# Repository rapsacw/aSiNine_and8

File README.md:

# aSiNine_and8
Small (46.5x73.2mm) BM1397 based standalone bitcoin miner

Revision 04k, remarks:
- PWM fan: do not populate T2,JP1 & R10, unless you want to use that feature (no software support yet), replace T2 with a mosfet if you want to use it, a transistor will pull gpio9 low at startup locking the esp in programming mode.
- programming first time: some esp's will not enter programming mode automatically, in that case short gpio9 to ground at power-up (gpio9 is connected to the encircled via close to the esp32-c3). Updating the firmware is best done through OTA @ <your miner's ip address>/update). You can also flash the esp with the ElegantOTA demo and then flash it first time over the air.
- Powering the miner: use a 5V/3A usb charger for low power application (upto ~250GHs). If you want more powerrr use the screw terminal to connect a 9-12V power supply. I use a usb trigger (like https://www.aliexpress.com/item/1005004562492420.html) set to 9V connected to a usb charger with PD (use a high efficiency charger like https://www.aliexpress.com/item/1005004530223949.html). IMPORTANT: only connect the miner with ONE of the power inputs. Powering the miner with more than 5V and connecting it to a PC will damage the miner and the pc!!!!
- Cooling: I use a 7cm piece of https://www.aliexpress.com/item/1005001772072504.html with a 5cm 5V fan (runs on 3.3V when connected to X1) like https://www.aliexpress.com/item/1005003059434065.html strapped to the heatsink and board with tie wraps. Don't forget to use some (non-conductive!) thermal compound. This fan/heatsink combo will allow the miner to be run at upto 320GHs while staying (just) below my max asic temperature of 60C and is virtually silent.
- The firmware used is bm1397.ino.bin included in this repo, and can be used until I update & publish the source code of my firmware.

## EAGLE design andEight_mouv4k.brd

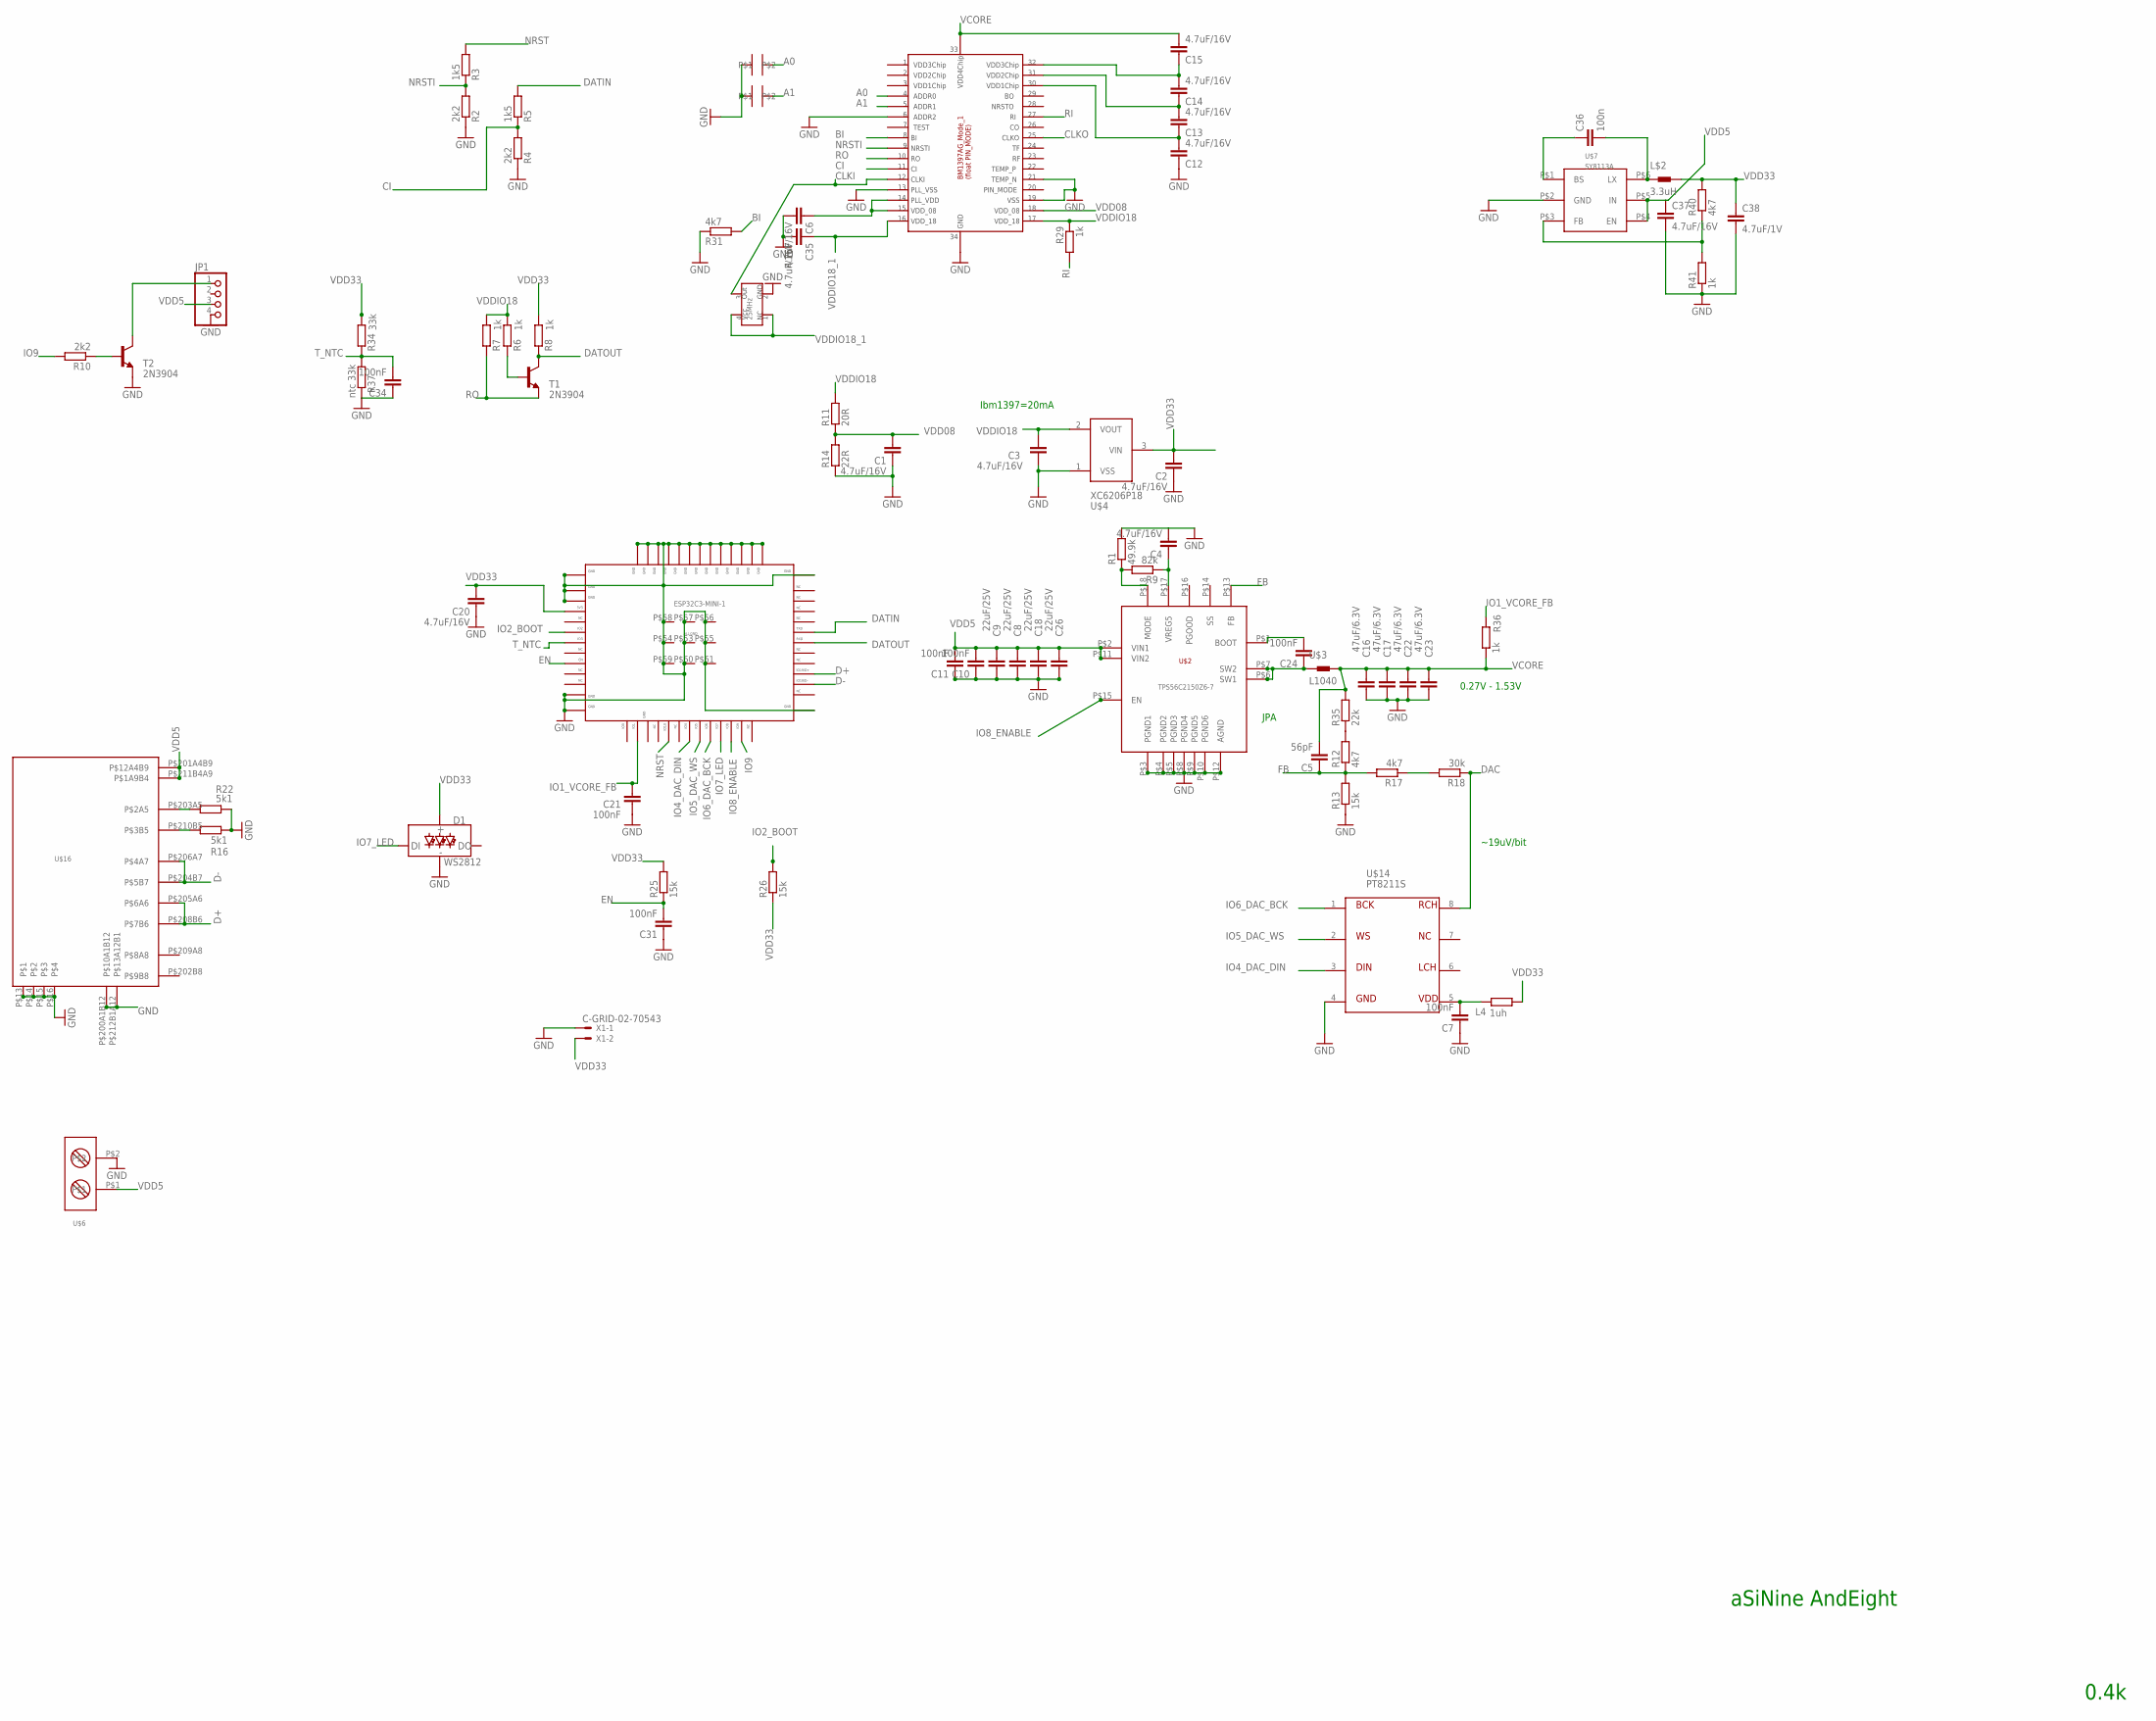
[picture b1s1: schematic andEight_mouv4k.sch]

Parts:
A0, A1: SOLDERJUMPER
C1, C2, C3, C4, C6, C12, C13, C14, C15, C35, C37: 4.7uF/16V; C0402
C5: 56pF; C0402
C7, C10, C11, C24, C31, C34: 100nF; C0402
C8, C9, C18, C26: 22uF/25V; C0805
C16, C17, C22, C23: 47uF/6.3V; C0805
C20: 4.7uF/16V; C0603
C21: 100nF; C0603
C36: 100n; C0402
C38: 4.7uF/1V; C0402
D1: WS2812; WS2812-5X5-4PIN
ESP32C3-MINI-1: ESP32-C3-MINI-1; ESP32C3MINI
JP1: PINHD-1X4/90; 1X04/90
L4: 1uh; R0402
L$2: 3.3uH; NR201610
R1: 49.9k; R0402
R2, R4, R10: 2k2; R0402
R3, R5: 1k5; R0402
R6, R7, R8, R29, R36, R41: 1k; R0402
R9: 82k; R0402
R11: 20R; R0402
R12, R17, R31, R40: 4k7; R0402
R13, R25, R26: 15k; R0402
R14: 22R; R0402
R16, R22: 5k1; R0402
R18: 30k; R0402
R34: 33k; R0603
R35: 22k; R0402
R37: ntc 33k; R0402
T1, T2: 2N3904; SOT23
U$1: BM1397-1; BM1391
U$2: TPS56C2150Z6-7; VQFN-HR
U$3: L1040
U$4: XC6206P18; SOT23
U$6: DG301-50
U$7: SY8113A; SOT23L-6
U$14: PT8211S; SO-8
U$16: USBCTHT; USBCSMTTHT
U$22: 25MHz; 3225
X1: C-GRID-02-70543; 70543-02

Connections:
A0: A0.P$1, U$1.P$4
A1: A1.P$1, U$1.P$5
BI: R31.2, U$1.P$8
CI: R4.2, R5.1, U$1.P$11
CLKI: U$1.P$12, U$22.P$3
CLKO: U$1.P$25
D+: ESP32C3-MINI-1.P$27, U$16.P$205A6 (P$6A6), U$16.P$208B6 (P$7B6)
D-: ESP32C3-MINI-1.P$26, U$16.P$204B7 (P$5B7), U$16.P$206A7 (P$4A7)
DAC: R18.1, U$14.8
DATIN: ESP32C3-MINI-1.P$31, R5.2
DATOUT: ESP32C3-MINI-1.P$30, R8.1, T1.3 (C)
EN: C31.2, ESP32C3-MINI-1.P$8, R25.1
FB: C5.1, R12.1, R13.2, R17.2, U$2.P$13 (FB)
GND: A0.P$2, A1.P$2, C1.1, C2.1, C3.1, C4.2, C6.2, C7.1, C8.2, C9.2, C10.1, C11.1, C12.1, C16.2, C17.2, C18.2, C20.1, C21.1, C22.2, C23.2, C26.2, C31.1, C34.1, C35.2, C37.2, C38.2, D1.GND, ESP32C3-MINI-1.P$1, ESP32C3-MINI-1.P$2, ESP32C3-MINI-1.P$11, ESP32C3-MINI-1.P$36, ESP32C3-MINI-1.P$37, ESP32C3-MINI-1.P$38, ESP32C3-MINI-1.P$39, ESP32C3-MINI-1.P$40, ESP32C3-MINI-1.P$41, ESP32C3-MINI-1.P$42, ESP32C3-MINI-1.P$43, ESP32C3-MINI-1.P$44, ESP32C3-MINI-1.P$45, ESP32C3-MINI-1.P$46, ESP32C3-MINI-1.P$47, ESP32C3-MINI-1.P$48, ESP32C3-MINI-1.P$49, ESP32C3-MINI-1.P$50, ESP32C3-MINI-1.P$51, ESP32C3-MINI-1.P$52, ESP32C3-MINI-1.P$53, ESP32C3-MINI-1.P$54, ESP32C3-MINI-1.P$55, ESP32C3-MINI-1.P$56, ESP32C3-MINI-1.P$57, ESP32C3-MINI-1.P$58, ESP32C3-MINI-1.P$59, ESP32C3-MINI-1.P$60, ESP32C3-MINI-1.P$61, JP1.4, R1.2, R2.1, R4.1, R13.1, R14.2, R16.2, R22.2, R31.1, R37.1, R41.1, T2.2 (E), U$1.P$6, U$1.P$13, U$1.P$19, U$1.P$21, U$1.P$34, U$2.P$3 (PGND1), U$2.P$4 (PGND2), U$2.P$5 (PGND3), U$2.P$8 (PGND4), U$2.P$9 (PGND5), U$2.P$10 (PGND6), U$2.P$12 (AGND), U$4.1 (VSS), U$6.P$2, U$7.P$2 (GND), U$14.4, U$16.P$13, U$16.P$14, U$16.P$15, U$16.P$16, U$16.P$200A1B12 (P$10A1B12), U$16.P$212B1A12 (P$13A12B1), U$22.P$2, X1.1
IO1_VCORE_FB: C21.2, ESP32C3-MINI-1.P$13, R36.2
IO2_BOOT: ESP32C3-MINI-1.P$5, R26.2
IO4_DAC_DIN: ESP32C3-MINI-1.P$18, U$14.3
IO5_DAC_WS: ESP32C3-MINI-1.P$19, U$14.2
IO6_DAC_BCK: ESP32C3-MINI-1.P$20, U$14.1
IO7_LED: D1.DI, ESP32C3-MINI-1.P$21
IO8_ENABLE: ESP32C3-MINI-1.P$22, U$2.P$15 (EN)
IO9: ESP32C3-MINI-1.P$23, R10.2
unnamed: R10.1, T2.1 (B)
unnamed: C24.2, U$2.P$1 (BOOT)
unnamed: C24.1, U$2.P$6 (SW1), U$2.P$7 (SW2), U$3.P$1 (1)
unnamed: C4.1, R9.1, U$2.P$17 (VREG5)
unnamed: R1.1, R9.2, U$2.P$18 (MODE)
unnamed: JP1.1, T2.3 (C)
unnamed: C36.1, U$7.P$1 (BS)
unnamed: C36.2, L$2.P$1 (1), U$7.P$6 (LX)
unnamed: R40.1, R41.2, U$7.P$3 (FB)
unnamed: R16.1, U$16.P$210B5 (P$3B5)
unnamed: R22.1, U$16.P$203A5 (P$2A5)
unnamed: R6.1, T1.1 (B)
unnamed: R12.2, R35.1
unnamed: R17.1, R18.2
NRST: ESP32C3-MINI-1.P$16, R3.2
NRSTI: R2.2, R3.1, U$1.P$9
P$5: C7.2, L4.2, U$14.5
RI: R29.2, U$1.P$27
RO: R7.1, T1.2 (E), U$1.P$10
T_NTC: C34.2, ESP32C3-MINI-1.P$6, R34.1, R37.2
VCORE: C5.2, C15.2, C16.1, C17.1, C22.1, C23.1, R35.2, R36.1, U$1.P$33, U$3.P$2 (2)
VDD1: C12.2, C13.1, U$1.P$30
VDD2: C13.2, C14.1, U$1.P$31
VDD3: C14.2, C15.1, U$1.P$32
VDD5: C8.1, C9.1, C10.2, C11.2, C18.1, C26.1, C37.1, JP1.3, U$2.P$2 (VIN1), U$2.P$11 (VIN2), U$6.P$1, U$7.P$4 (EN), U$7.P$5 (IN), U$16.P$201A4B9 (P$12A4B9), U$16.P$211B4A9 (P$1A9B4)
VDD08: C1.2, R11.2, R14.1, U$1.P$18
VDD08_1: C6.1, U$1.P$14, U$1.P$15
VDD33: C2.2, C20.2, C38.1, D1.VCC, ESP32C3-MINI-1.P$3, L4.1, L$2.P$2 (2), R8.2, R25.2, R26.1, R34.2, R40.2, U$4.3 (VIN), X1.2
VDDIO18: C3.2, R6.2, R7.2, R11.1, R29.1, U$1.P$17, U$4.2 (VOUT)
VDDIO18_1: C35.1, U$1.P$16, U$22.P$1, U$22.P$4

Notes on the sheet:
0.27V - 1.53V
JPA
aSiNine AndEight
0.4k
~19uV/bit
Ibm1397=20mA

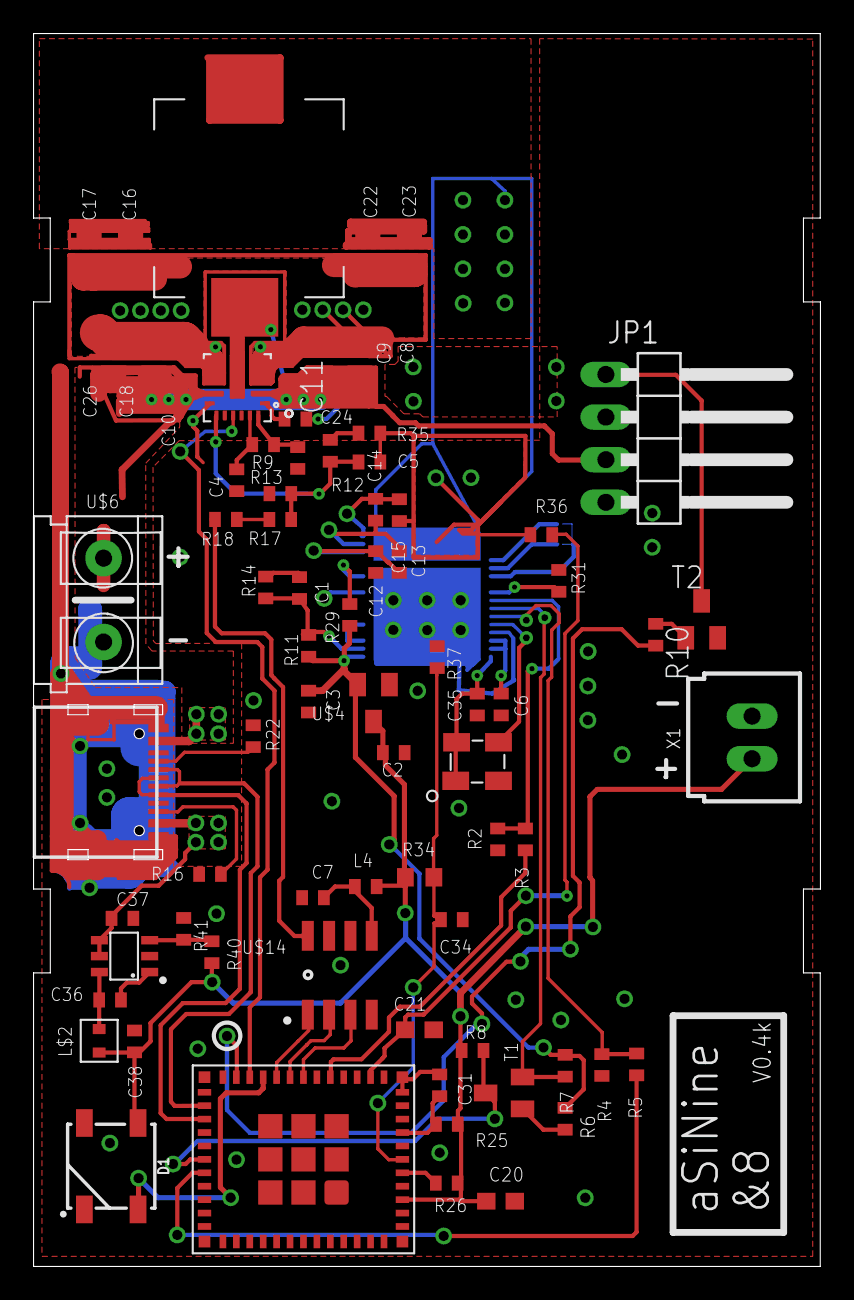
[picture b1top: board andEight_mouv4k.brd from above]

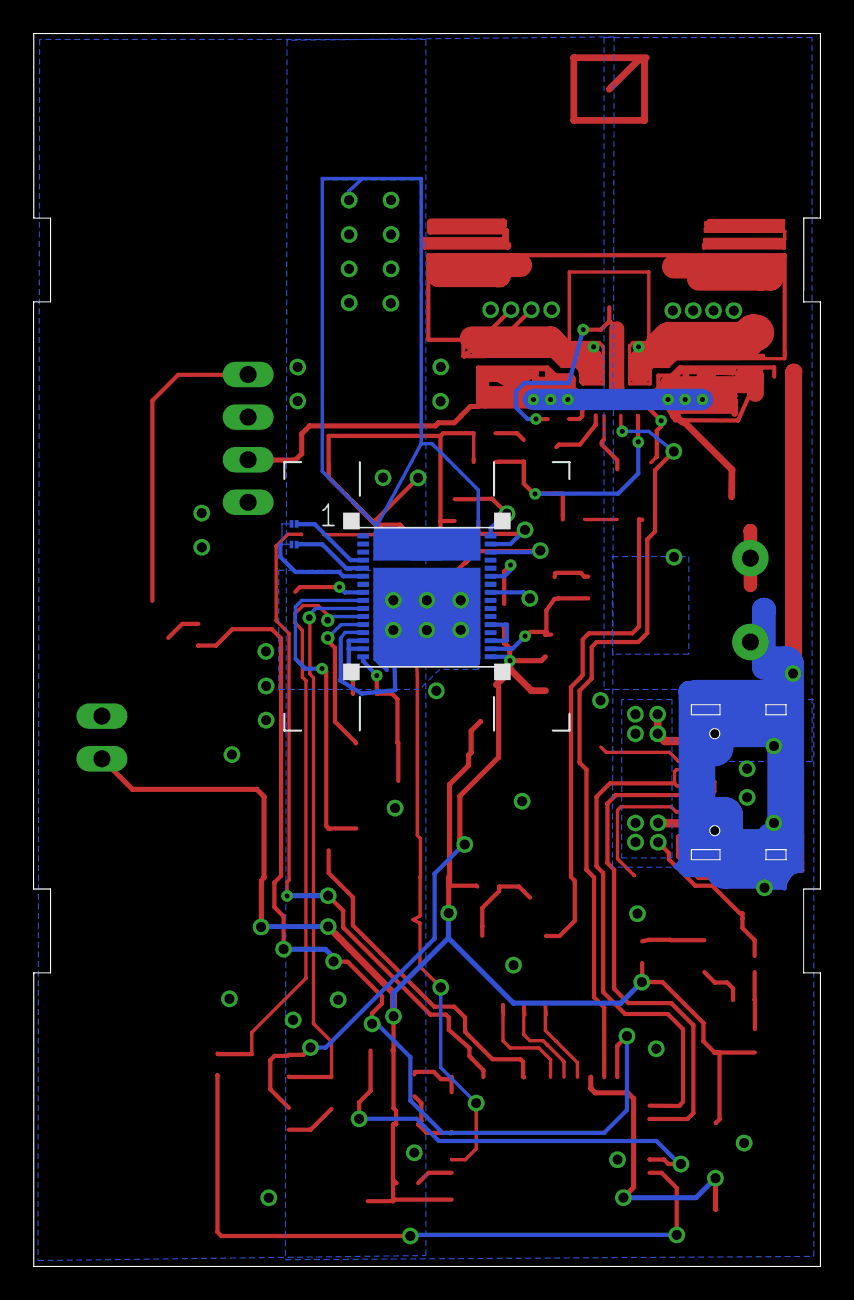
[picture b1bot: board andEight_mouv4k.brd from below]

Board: 2 copper layers, 46.9 x 73.5 mm, 77 parts (3 on the bottom side), 51 nets.

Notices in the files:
parts and their libraries:
SparkFun-LED: Licensing: Creative Commons ShareAlike 4.0 International - https://creativecommons.org/licenses/by-sa/4.0
